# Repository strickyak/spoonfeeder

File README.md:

# spoonfeeder
experimental idea for booting a Radio Shack Color Computer by a Pi Pico(W) by Spoonfeeding

Based on this Proto Board:
https://raw.githubusercontent.com/JayesonLS/TandyCircuitsAndLogic/master/CoCoProtoBoard/CoCoProtoBoard.png

## Working Spoonfeeder for 1/2-text-screen SemiGraphics Game on Aardvark

Plug Aardvark into coco2.

Load micropy/step5.py into Thonny.

Turn on the coco2.  The screen will be frozen.
That's because the Aardvark is holding HALT down,
and waiting until it sees a RESET.

So click the RESET on the back of the coco2.

You should see this in the Thonny console:

```
MPY: soft reboot
Step2: waiting for RESET.
got RESET.
debounced.
RESET gone.
SLEPT half a second.
Activated onreset prog.  Deactivating.

(0034ccff, 000002fd) Activated sm2. Deactivating.
(0060ccff, 000102fd) Activated sm2. Deactivating.
```

And the coco2, after spoonfeeding all the bytes,
should be playing Life on the upper half of the
screen.   There will just be dots on the lower half.

Why only half the screen?  I wanted this to work on
a 4K coco1, and I didn't have enough RAM for the
extra Life arrays in the code that I wrote,
if the screen was full-sized.

## Demo of Control Write & Data Read on Aardvark

`sunday/alfadown-ff7b.py` was not outputting stuff
correctly when I last touched it.

But thanks to Phoenix and Thomas, they fixed the
problem with Pin Directions.  I was using a PIO opcode
that doesn't work for Pin Directions.

A small BASIC program can be typed in to make
the demo work:

```
10 POKE &HFF7A, 22  : REM write any byte to Control Port
20 FOR I=1 TO 8
30 X = PEEK(&HFF7B)
40 PRINT X, CHR$(X)
50 NEXT I
```

When that is run, the POKE to the control port will
enable the Data Port machine to operate.  Then we can
read the "Hello world..." message.  That FOR loop
just reads the first 8 bytes of the message.

Also if you want the Pico W to power up into a more
sane state -- so it doesn't cause the coco to stall
(due the the HALT being low) -- load `sunday/aard_boot.py`
into the Pico's filesystem with the name `boot.py`.

## END

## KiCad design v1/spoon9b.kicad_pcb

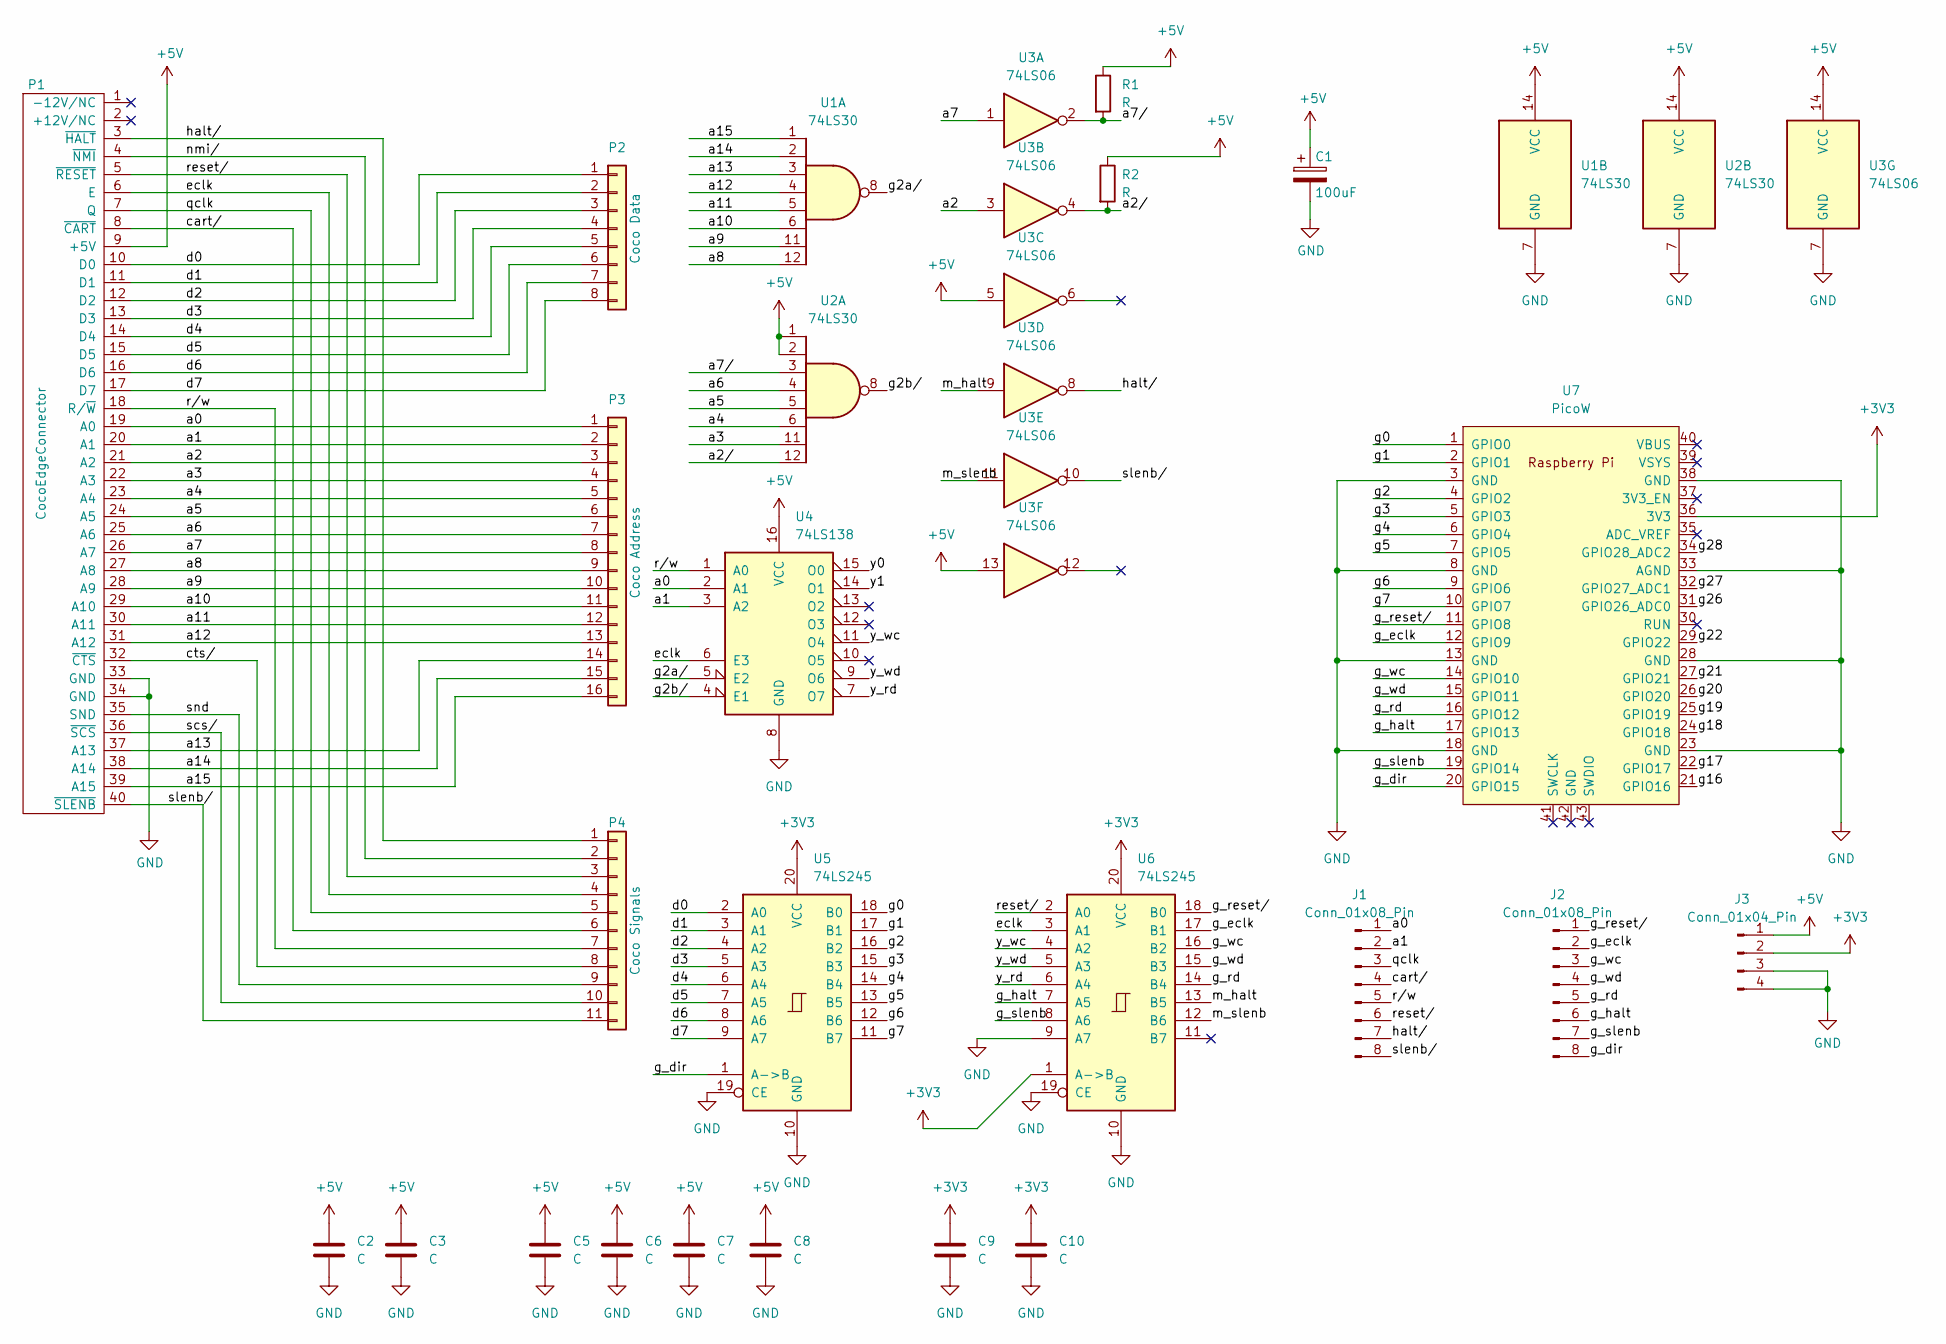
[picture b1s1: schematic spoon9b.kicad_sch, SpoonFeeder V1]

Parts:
C1: 100uF; C_Radial_D7.5_L11.2_P2.5
C2, C3, C5, C6, C7, C8, C9, C10: C; C_Disc_D5.0mm_W2.5mm_P5.00mm
J1, J2: Conn_01x08_Pin; PinHeader_1x08_P2.54mm_Vertical
J3: Conn_01x04_Pin; PinHeader_1x04_P2.54mm_Vertical
P1: CocoEdgeConnector; CocoCardEdgeCocoMIDI
P2: Coco Data; DIP-16_W7.62mm
P3: Coco Address; DIP-32_W15.24mm
P4: Coco Signals; DIP-22_W10.16mm
R1, R2: R; R_Axial_DIN0207_L6.3mm_D2.5mm_P10.16mm_Horizontal
U1, U2: 74LS30; DIP-14_W7.62mm_LongPads
U3: 74LS06; DIP-14_W7.62mm_LongPads
U4: 74LS138; DIP-16_W7.62mm_LongPads
U5, U6: 74LS245; DIP-20_W7.62mm_LongPads
U7: PicoW; RPi_PicoW_SMD_TH

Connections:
+3V3: C9.1, C10.1, J3.2, U5.20 (VCC), U6.1 (A->B), U6.20 (VCC), U7.36 (3V3)
+5V: C1.1, C2.1, C3.1, C5.1, C6.1, C7.1, C8.1, J3.1, P1.9 (+5V), R1.1, R2.1, U1.14 (VCC), U2.1, U2.2, U2.14 (VCC), U3.5, U3.13, U3.14 (VCC), U4.16 (VCC)
/a0: J1.1, P1.19 (A0), P3.1, U4.2 (A1)
/a1: J1.2, P1.20 (A1), P3.2, U4.3 (A2)
/a2: P1.21 (A2), P3.3, U3.3
/a2/: R2.2, U2.12, U3.4
/a3: P1.22 (A3), P3.4, U2.11
/a4: P1.23 (A4), P3.5, U2.6
/a5: P1.24 (A5), P3.6, U2.5
/a6: P1.25 (A6), P3.7, U2.4
/a7: P1.26 (A7), P3.8, U3.1
/a7/: R1.2, U2.3, U3.2
/a8: P1.27 (A8), P3.9, U1.12
/a9: P1.28 (A9), P3.10, U1.11
/a10: P1.29 (A10), P3.11, U1.6
/a11: P1.30 (A11), P3.12, U1.5
/a12: P1.31 (A12), P3.13, U1.4
/a13: P1.37 (A13), P3.14, U1.3
/a14: P1.38 (A14), P3.15, U1.2
/a15: P1.39 (A15), P3.16, U1.1
/cart/: J1.4, P1.8 (~CART), P4.6
/cts/: P1.32 (~CTS), P4.8
/d0: P1.10 (D0), P2.1, U5.2 (A0)
/d1: P1.11 (D1), P2.2, U5.3 (A1)
/d2: P1.12 (D2), P2.3, U5.4 (A2)
/d3: P1.13 (D3), P2.4, U5.5 (A3)
/d4: P1.14 (D4), P2.5, U5.6 (A4)
/d5: P1.15 (D5), P2.6, U5.7 (A5)
/d6: P1.16 (D6), P2.7, U5.8 (A6)
/d7: P1.17 (D7), P2.8, U5.9 (A7)
/eclk: P1.6 (E), P4.4, U4.6 (E3), U6.3 (A1)
/g0: U5.18 (B0), U7.1 (GPIO0)
/g1: U5.17 (B1), U7.2 (GPIO1)
/g2: U5.16 (B2), U7.4 (GPIO2)
/g2a/: U1.8, U4.5 (E2)
/g2b/: U2.8, U4.4 (E1)
/g3: U5.15 (B3), U7.5 (GPIO3)
/g4: U5.14 (B4), U7.6 (GPIO4)
/g5: U5.13 (B5), U7.7 (GPIO5)
/g6: U5.12 (B6), U7.9 (GPIO6)
/g7: U5.11 (B7), U7.10 (GPIO7)
/g16: U7.21 (GPIO16)
/g17: U7.22 (GPIO17)
/g18: U7.24 (GPIO18)
/g19: U7.25 (GPIO19)
/g20: U7.26 (GPIO20)
/g21: U7.27 (GPIO21)
/g22: U7.29 (GPIO22)
/g26: U7.31 (GPIO26_ADC0)
/g27: U7.32 (GPIO27_ADC1)
/g28: U7.34 (GPIO28_ADC2)
/g_dir: J2.8, U5.1 (A->B), U7.20 (GPIO15)
/g_eclk: J2.2, U6.17 (B1), U7.12 (GPIO9)
/g_halt: J2.6, U6.7 (A5), U7.17 (GPIO13)
/g_rd: J2.5, U6.14 (B4), U7.16 (GPIO12)
/g_reset/: J2.1, U6.18 (B0), U7.11 (GPIO8)
/g_slenb: J2.7, U6.8 (A6), U7.19 (GPIO14)
/g_wc: J2.3, U6.16 (B2), U7.14 (GPIO10)
/g_wd: J2.4, U6.15 (B3), U7.15 (GPIO11)
/halt/: J1.7, P1.3 (~HALT), P4.1, U3.8
/m_halt: U3.9, U6.13 (B5)
/m_slenb: U3.11, U6.12 (B6)
/nmi/: P1.4 (~NMI), P4.2
/qclk: J1.3, P1.7 (Q), P4.5
/reset/: J1.6, P1.5 (~RESET), P4.3, U6.2 (A0)
/r/w: J1.5, P1.18 (R/~W), P4.7, U4.1 (A0)
/scs/: P1.36 (~SCS), P4.10
/slenb/: J1.8, P1.40 (~SLENB), P4.11, U3.10
/snd: P1.35 (SND), P4.9
/y0: U4.15 (O0)
/y1: U4.14 (O1)
/y_rd: U4.7 (O7), U6.6 (A4)
/y_wc: U4.11 (O4), U6.4 (A2)
/y_wd: U4.9 (O6), U6.5 (A3)
GND: C1.2, C2.2, C3.2, C5.2, C6.2, C7.2, C8.2, C9.2, C10.2, J3.3, J3.4, P1.33 (GND), P1.34 (GND), U1.7 (GND), U2.7 (GND), U3.7 (GND), U4.8 (GND), U5.10 (GND), U5.19 (CE), U6.9 (A7), U6.10 (GND), U6.19 (CE), U7.3 (GND), U7.8 (GND), U7.13 (GND), U7.18 (GND), U7.23 (GND), U7.28 (GND), U7.33 (AGND), U7.38 (GND); also elsewhere on the board

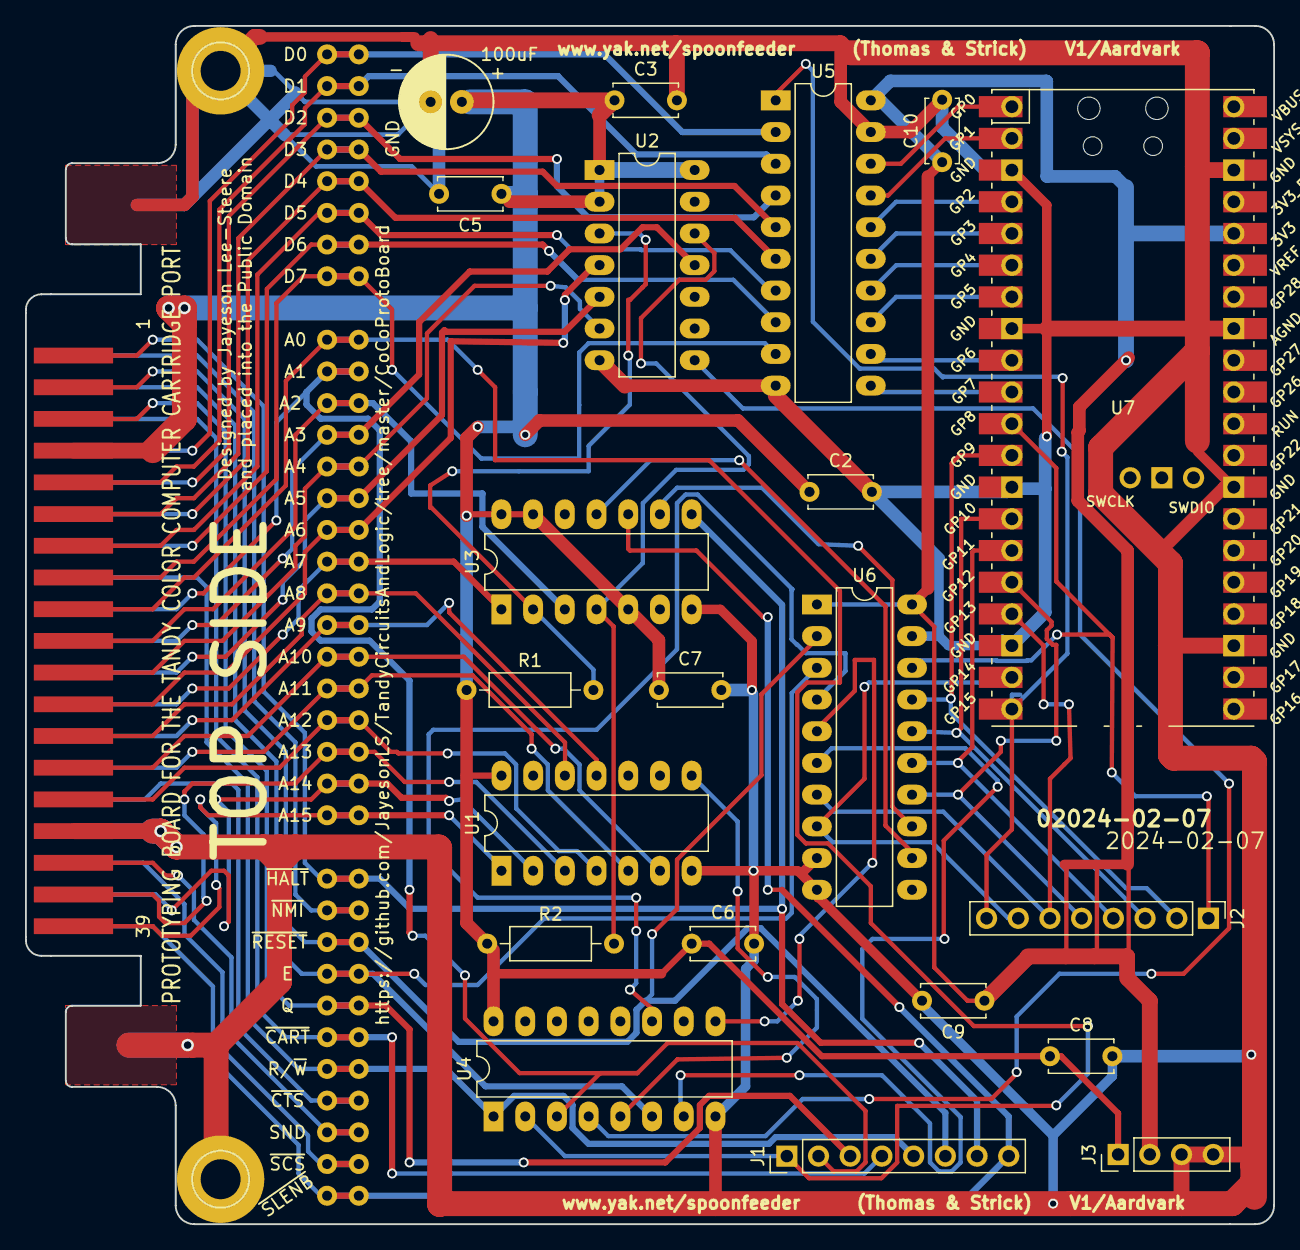
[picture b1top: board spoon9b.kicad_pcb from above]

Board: 2 copper layers, 100.0 x 96.0 mm, 27 parts (0 on the bottom side), 63 nets.

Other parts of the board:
aREF**: 1pin
bREF**: 1pin

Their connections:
GND: aREF**.1, bREF**.1; also elsewhere on the board

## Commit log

2024-02-13 Update README.md
    credit proto board
2024-02-13 initial v1/ checkin
2024-02-14 step1 (send reset vector) in micropy
2024-02-15 add copico board v1 from Thomas
2024-02-15 spoonfeeding: step2-ldd-std-into-screen-memory.py
2024-02-15 add copico-sane-null.py for copico board.
2024-02-16 step3 (wc-wd-rd) loop
2024-02-16 io_ff78-read-255-of-data.c
2024-02-16 add thomas-step2 which works on copico v1.
2024-02-17 life-semi.c (in micropy)
2024-02-18 step5 works for life-semi in 4K RAM
2024-02-18 carrier-copico-py & copico5.py for Copico
2024-02-18 carrier-copico-py fixed and runs on copico
2024-02-18 adding copico5 so it doesn't have to be built
2024-02-19 life-semi.c with -O2 not -Os
2024-02-25 sunday directory
2024-02-25 make both decb and raw
2024-02-25 make pico-reader.lemma
2024-02-25 add sunday/burn-hints.txt
2024-02-25 end print with ; not ,
2024-02-26 alfadown-ff7b.py for Aardvark/V1
2024-02-27 debugging with alfadown-ff7b.py, see NANDO.
2024-04-18 Fix uPy script that replies to ff7b
    Fix the following issues with the MicroPython script that
    replies to ff7b:
    - Output from 74LS138 is active-low; correct logic to account
    for this.
    - pindirs cannot be SET; use OUT instead
    Also, clean up and comment the code.
2024-04-18 old changes (io_ff78-read-255-of-data.c)
2024-04-22 Request for comments on proto1.asm
2024-04-22 update README about spoonfeeding.
2024-04-22 Add boot.py w/ sane pico boot-time defaults
2024-04-22 readme about control write data read demo
2024-04-22 Print the control write byte received in ..ff7b.py
2024-04-23 add wiznet idea
2024-04-23 add URL
2024-04-23 mention Pi Pico W in title
2024-04-24 Update ..-ff7b.py to restart after control write
    Update the ..-ff7b.py script to wait until a control write of 0x01 to start
    sending bytes to the CoCo in response to data reads, and to restart the string
    it is sending whenever another 0x01 control write is received.
2024-04-26 Add RESET (0x00) Control Port operation
    Add a RESET operation on the Control Port. This will cause the CoPiCo NETIO
    function to stop replying to Data Port reads as well as (in the future)
    dropping the network connection.
    Clear the TX FIFO on the Data Read PIO state machine after a RESET operation is
    received.
2024-04-28 ..-ff7b.py: Stop sending at end of text
    Stop sending data back to the CoCo in response to 0xFF7B reads when we reach
    the end of the text.
2024-04-28 ..-ff7b.py: Use byte string for bytes to send
    ... and other cleanup
2024-04-30 ..-ff7b.py: Release PIOs etc so uPy doesn't crash
    Micropython has been running out of resources after aborting the ..-ff7b.py
    script. Add code to explicitly release these resources and run a garbage
    collection.
    Also, clean up comments, VSCode warnings, etc.
2024-04-30 ..-ff7b.py: Use DMA to send bytes to SM for CoCo
2024-05-01 ..-ff7b.py: Clean up DMA code
    Clean up DMA code in preparation for it becoming a separate library.
2024-05-02 ..-ff7b.py: Make PIO, DMA handling object oriented
2024-05-02 ..-ff7b.py: Create abst base cls; explain file
    Add an abstract base class (or the closest thing we have on MicroPython) for
    the DataProducters (CPU and DMA).
    Add an explanation of what this module does to the top of the module.
    TODO: Make that comment into a module docstring.
2024-05-03 Rename/move ..-ff7b.py to netio.py
    * Rename sunday/alfadown-ff7b.py to netio/netio.py
    * Also move the two modules used by netio.py to the same directory
2024-05-04 netio: Change text of test string

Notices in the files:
v1/spoon9b.kicad_pcb:
and placed into the Public Domain
